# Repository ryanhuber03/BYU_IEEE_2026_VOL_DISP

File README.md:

# BYU_IEEE_2026_VOL_DISP
Volumetric Display for the BYU IEEE student branch, fall 2026.

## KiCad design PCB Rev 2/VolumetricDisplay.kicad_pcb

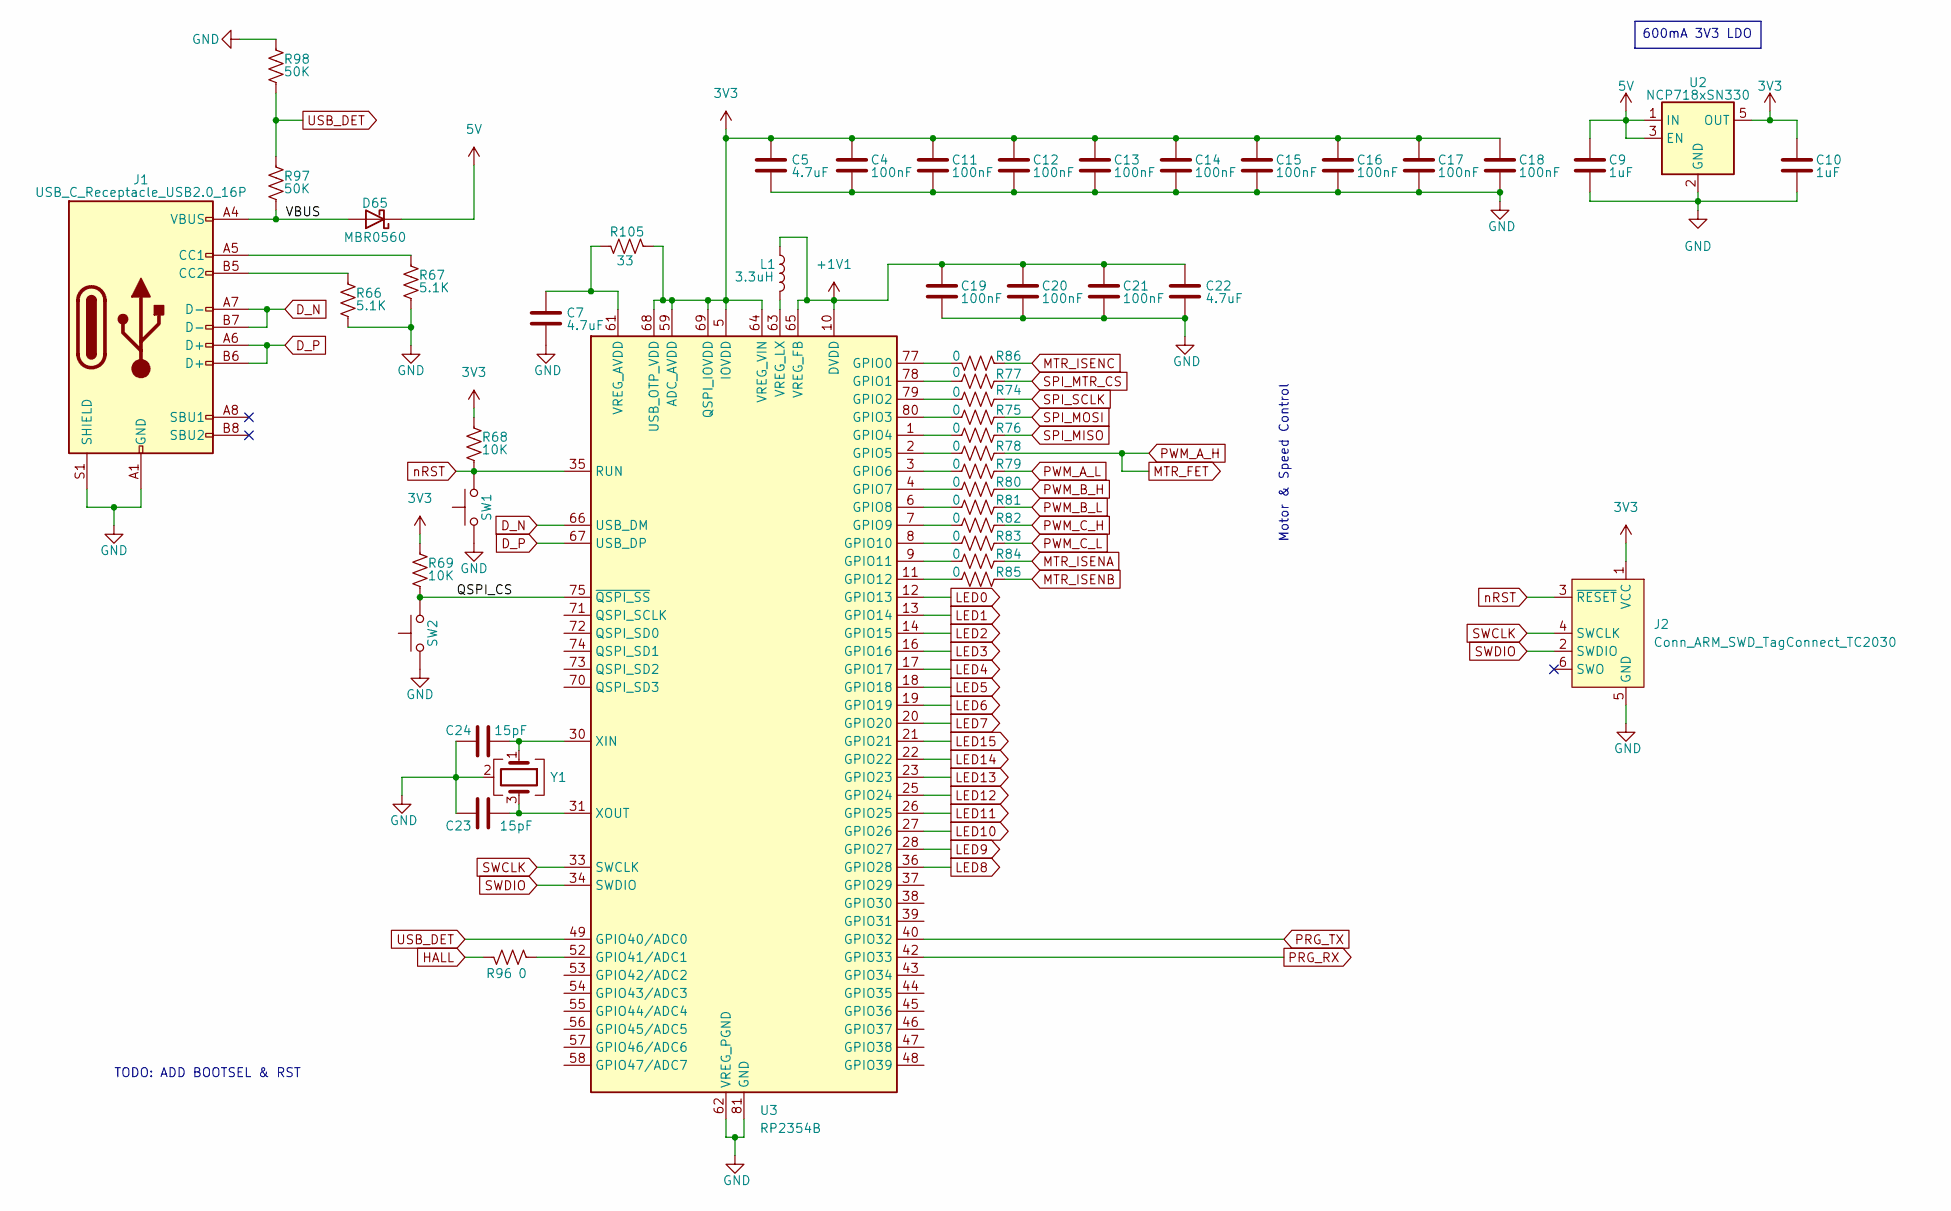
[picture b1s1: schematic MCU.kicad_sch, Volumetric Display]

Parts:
C4, C11, C12, C13, C14, C15, C16, C17, C18, C19, C20, C21: 100nF; C_0402_1005Metric_Pad0.74x0.62mm_HandSolder
C5, C7, C22: 4.7uF; C_0402_1005Metric_Pad0.74x0.62mm_HandSolder
C9, C10: 1uF; C_0603_1608Metric_Pad1.08x0.95mm_HandSolder
C23, C24: 15pF; C_0402_1005Metric_Pad0.74x0.62mm_HandSolder
D65: MBR0560; D_SOD-123
J1: USB_C_Receptacle_USB2.0_16P; USB_C_Receptacle_GCT_USB4085
J2: Conn_ARM_SWD_TagConnect_TC2030; Tag-Connect_TC2030-IDC-NL_2x03_P1.27mm_Vertical
L1: 3.3uH; L_0805_2012Metric_Pad1.05x1.20mm_HandSolder
R66, R67: 5.1K; R_0603_1608Metric_Pad0.98x0.95mm_HandSolder
R68, R69: 10K; R_0603_1608Metric_Pad0.98x0.95mm_HandSolder
R74, R75, R76, R77, R78, R79, R80, R81, R82, R83, R84, R85, R86, R96: 0; R_0603_1608Metric_Pad0.98x0.95mm_HandSolder
R97, R98: 50K; R_0603_1608Metric_Pad0.98x0.95mm_HandSolder
R105: 33; R_0603_1608Metric_Pad0.98x0.95mm_HandSolder
SW1, SW2: TS-1088-AR02016; SW_TS-1088-AR02016
U2: NCP718xSN330; SOT-23-5
U3: RP2354B; QFN-80-1EP_10x10mm_P0.4mm_EP3.4x3.4mm
Y1: Abracon ABM8-272-T3; Crystal_SMD_Abracon_ABM8G-4Pin_3.2x2.5mm

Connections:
3V3: C4.1, C5.1, C10.1, C11.1, C12.1, C13.1, C14.1, C15.1, C16.1, C17.1, C18.1, J2.1 (VCC), R68.2, R69.2, R105.1, U2.5 (OUT), U3.5 (IOVDD), U3.15 (IOVDD), U3.24 (IOVDD), U3.29 (IOVDD), U3.41 (IOVDD), U3.50 (IOVDD), U3.59 (ADC_AVDD), U3.60 (IOVDD), U3.64 (VREG_VIN), U3.68 (USB_OTP_VDD), U3.69 (QSPI_IOVDD), U3.76 (IOVDD); also elsewhere on the board
5V: C9.1, D65.1 (K), U2.1 (IN), U2.3 (EN); also elsewhere on the board
+1V1: C19.1, C20.1, C21.1, C22.1, L1.1, U3.10 (DVDD), U3.32 (DVDD), U3.51 (DVDD), U3.65 (VREG_FB)
/MCU/QSPI_CS: R69.1, SW2.2, U3.75 (~QSPI_SS)
/MCU/VBUS: D65.2 (A), J1.A4 (VBUS), J1.A9 (VBUS), J1.B4 (VBUS), J1.B9 (VBUS), R97.1
D_N: J1.A7 (D-), J1.B7 (D-), U3.66 (USB_DM)
D_P: J1.A6 (D+), J1.B6 (D+), U3.67 (USB_DP)
GND: C4.2, C5.2, C7.2, C9.2, C10.2, C11.2, C12.2, C13.2, C14.2, C15.2, C16.2, C17.2, C18.2, C19.2, C20.2, C21.2, C22.2, C23.1, C24.1, J1.A1 (GND), J1.A12 (GND), J1.B1 (GND), J1.B12 (GND), J1.S1 (SHIELD), J2.5 (GND), R66.1, R67.1, R98.2, SW1.1, SW2.1, U2.2 (GND), U3.62 (VREG_PGND), U3.81 (GND), Y1.2 (G), Y1.4 (G); also elsewhere on the board
HALL: R96.2; also elsewhere on the board
LED0: U3.12 (GPIO13); also elsewhere on the board
LED1: U3.13 (GPIO14); also elsewhere on the board
LED2: U3.14 (GPIO15); also elsewhere on the board
LED3: U3.16 (GPIO16); also elsewhere on the board
LED4: U3.17 (GPIO17); also elsewhere on the board
LED5: U3.18 (GPIO18); also elsewhere on the board
LED6: U3.19 (GPIO19); also elsewhere on the board
LED7: U3.20 (GPIO20); also elsewhere on the board
LED8: U3.36 (GPIO28); also elsewhere on the board
LED9: U3.28 (GPIO27); also elsewhere on the board
LED10: U3.27 (GPIO26); also elsewhere on the board
LED11: U3.26 (GPIO25); also elsewhere on the board
LED12: U3.25 (GPIO24); also elsewhere on the board
LED13: U3.23 (GPIO23); also elsewhere on the board
LED14: U3.22 (GPIO22); also elsewhere on the board
LED15: U3.21 (GPIO21); also elsewhere on the board
MTR_FET: R78.2; also elsewhere on the board
MTR_ISENA: R84.2; also elsewhere on the board
MTR_ISENB: R85.2; also elsewhere on the board
MTR_ISENC: R86.2; also elsewhere on the board
unnamed: J1.A5 (CC1), R67.2
unnamed: J1.B5 (CC2), R66.2
unnamed: R86.1, U3.77 (GPIO0)
unnamed: R77.1, U3.78 (GPIO1)
unnamed: R74.1, U3.79 (GPIO2)
unnamed: R75.1, U3.80 (GPIO3)
unnamed: R76.1, U3.1 (GPIO4)
unnamed: R78.1, U3.2 (GPIO5)
unnamed: R79.1, U3.3 (GPIO6)
unnamed: R80.1, U3.4 (GPIO7)
unnamed: R81.1, U3.6 (GPIO8)
unnamed: R82.1, U3.7 (GPIO9)
unnamed: R83.1, U3.8 (GPIO10)
unnamed: R84.1, U3.9 (GPIO11)
unnamed: R85.1, U3.11 (GPIO12)
unnamed: R96.1, U3.52 (GPIO41/ADC1)
unnamed: C7.1, R105.2, U3.61 (VREG_AVDD)
unnamed: L1.2, U3.63 (VREG_LX)
unnamed: C24.2, U3.30 (XIN), Y1.1
unnamed: C23.2, U3.31 (XOUT), Y1.3
PRG_RX: U3.42 (GPIO33)
PRG_TX: U3.40 (GPIO32)
PWM_A_L: R79.2; also elsewhere on the board
PWM_B_H: R80.2; also elsewhere on the board
PWM_B_L: R81.2; also elsewhere on the board
PWM_C_H: R82.2; also elsewhere on the board
PWM_C_L: R83.2; also elsewhere on the board
SPI_MISO: R76.2; also elsewhere on the board
SPI_MOSI: R75.2; also elsewhere on the board
SPI_MTR_CS: R77.2; also elsewhere on the board
SPI_SCLK: R74.2; also elsewhere on the board
SWCLK: J2.4 (SWCLK), U3.33 (SWCLK)
SWDIO: J2.2 (SWDIO), U3.34 (SWDIO)
USB_DET: R97.2, R98.1, U3.49 (GPIO40/ADC0)
nRST: J2.3 (~RESET), R68.1, SW1.2, U3.35 (RUN)

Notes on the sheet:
Motor & Speed Control
TODO: ADD BOOTSEL & RST
600mA 3V3 LDO

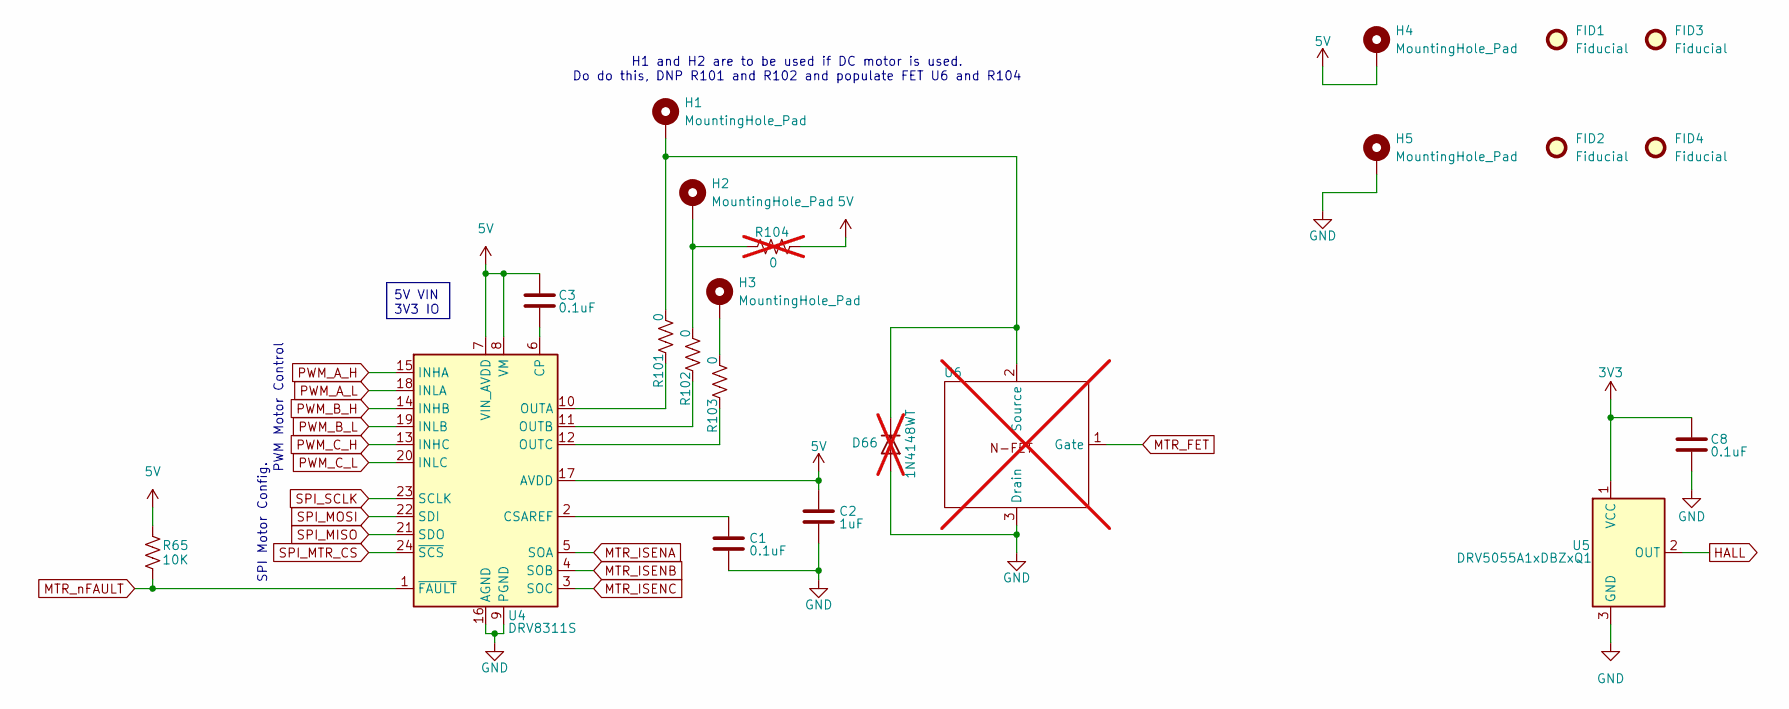
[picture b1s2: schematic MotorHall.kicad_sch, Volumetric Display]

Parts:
C1, C3: 0.1uF; C_0402_1005Metric_Pad0.74x0.62mm_HandSolder
C2: 1uF; C_0402_1005Metric_Pad0.74x0.62mm_HandSolder
C8: 0.1uF; C_0603_1608Metric_Pad1.08x0.95mm_HandSolder
D66: 1N4148WT; D_SOD-323_HandSoldering; not fitted
FID1, FID2, FID3, FID4: Fiducial; Fiducial_0.5mm_Mask1mm
H1, H2, H3, H4, H5: MountingHole_Pad; 28AWG Pad
R65: 10K; R_0603_1608Metric_Pad0.98x0.95mm_HandSolder
R101, R102, R103: 0; R_0603_1608Metric_Pad0.98x0.95mm_HandSolder
R104: 0; R_0603_1608Metric_Pad0.98x0.95mm_HandSolder; not fitted
U4: DRV8311S; Texas_RRW0024A_WQFN-24-1EP_3x3mm_P0.4mm_EP1.9x1.9mm
U5: DRV5055A1xDBZxQ1; SOT-23
U6: SOT-23_Handsoldering; not fitted

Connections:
3V3: C8.2, U5.1 (VCC); also elsewhere on the board
5V: C2.1, C3.2, H4.1 (1_1), R65.1, R104.1, U4.7 (VIN_AVDD), U4.8 (VM), U4.17 (AVDD); also elsewhere on the board
GND: C1.1, C2.2, C8.1, D66.2 (A), H5.1 (1_1), U4.9 (PGND), U4.16 (AGND), U4.25 (PGND), U5.3 (GND), U6.3 (Drain); also elsewhere on the board
HALL: U5.2 (OUT); also elsewhere on the board
MTR_FET: U4.15 (INHA), U6.1 (Gate); also elsewhere on the board
MTR_ISENA: U4.5 (SOA); also elsewhere on the board
MTR_ISENB: U4.4 (SOB); also elsewhere on the board
MTR_ISENC: U4.3 (SOC); also elsewhere on the board
MTR_nFAULT: R65.2, U4.1 (~FAULT)
unnamed: D66.1 (K), H1.1 (1_1), R101.1, U6.2 (Source)
unnamed: H2.1 (1_1), R102.1, R104.2
unnamed: H3.1 (1_1), R103.1
unnamed: C3.1, U4.6 (CP)
unnamed: C1.2, U4.2 (CSAREF)
unnamed: R101.2, U4.10 (OUTA)
unnamed: R102.2, U4.11 (OUTB)
unnamed: R103.2, U4.12 (OUTC)
PWM_A_L: U4.18 (INLA); also elsewhere on the board
PWM_B_H: U4.14 (INHB); also elsewhere on the board
PWM_B_L: U4.19 (INLB); also elsewhere on the board
PWM_C_H: U4.13 (INHC); also elsewhere on the board
PWM_C_L: U4.20 (INLC); also elsewhere on the board
SPI_MISO: U4.21 (SDO); also elsewhere on the board
SPI_MOSI: U4.22 (SDI); also elsewhere on the board
SPI_MTR_CS: U4.24 (~SCS); also elsewhere on the board
SPI_SCLK: U4.23 (SCLK); also elsewhere on the board

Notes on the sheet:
PWM Motor Control
H1 and H2 are to be used if DC motor is used. Do do this, DNP R101 and R102 and populate FET U6 and R104
SPI Motor Config.
5V VIN 3V3 IO

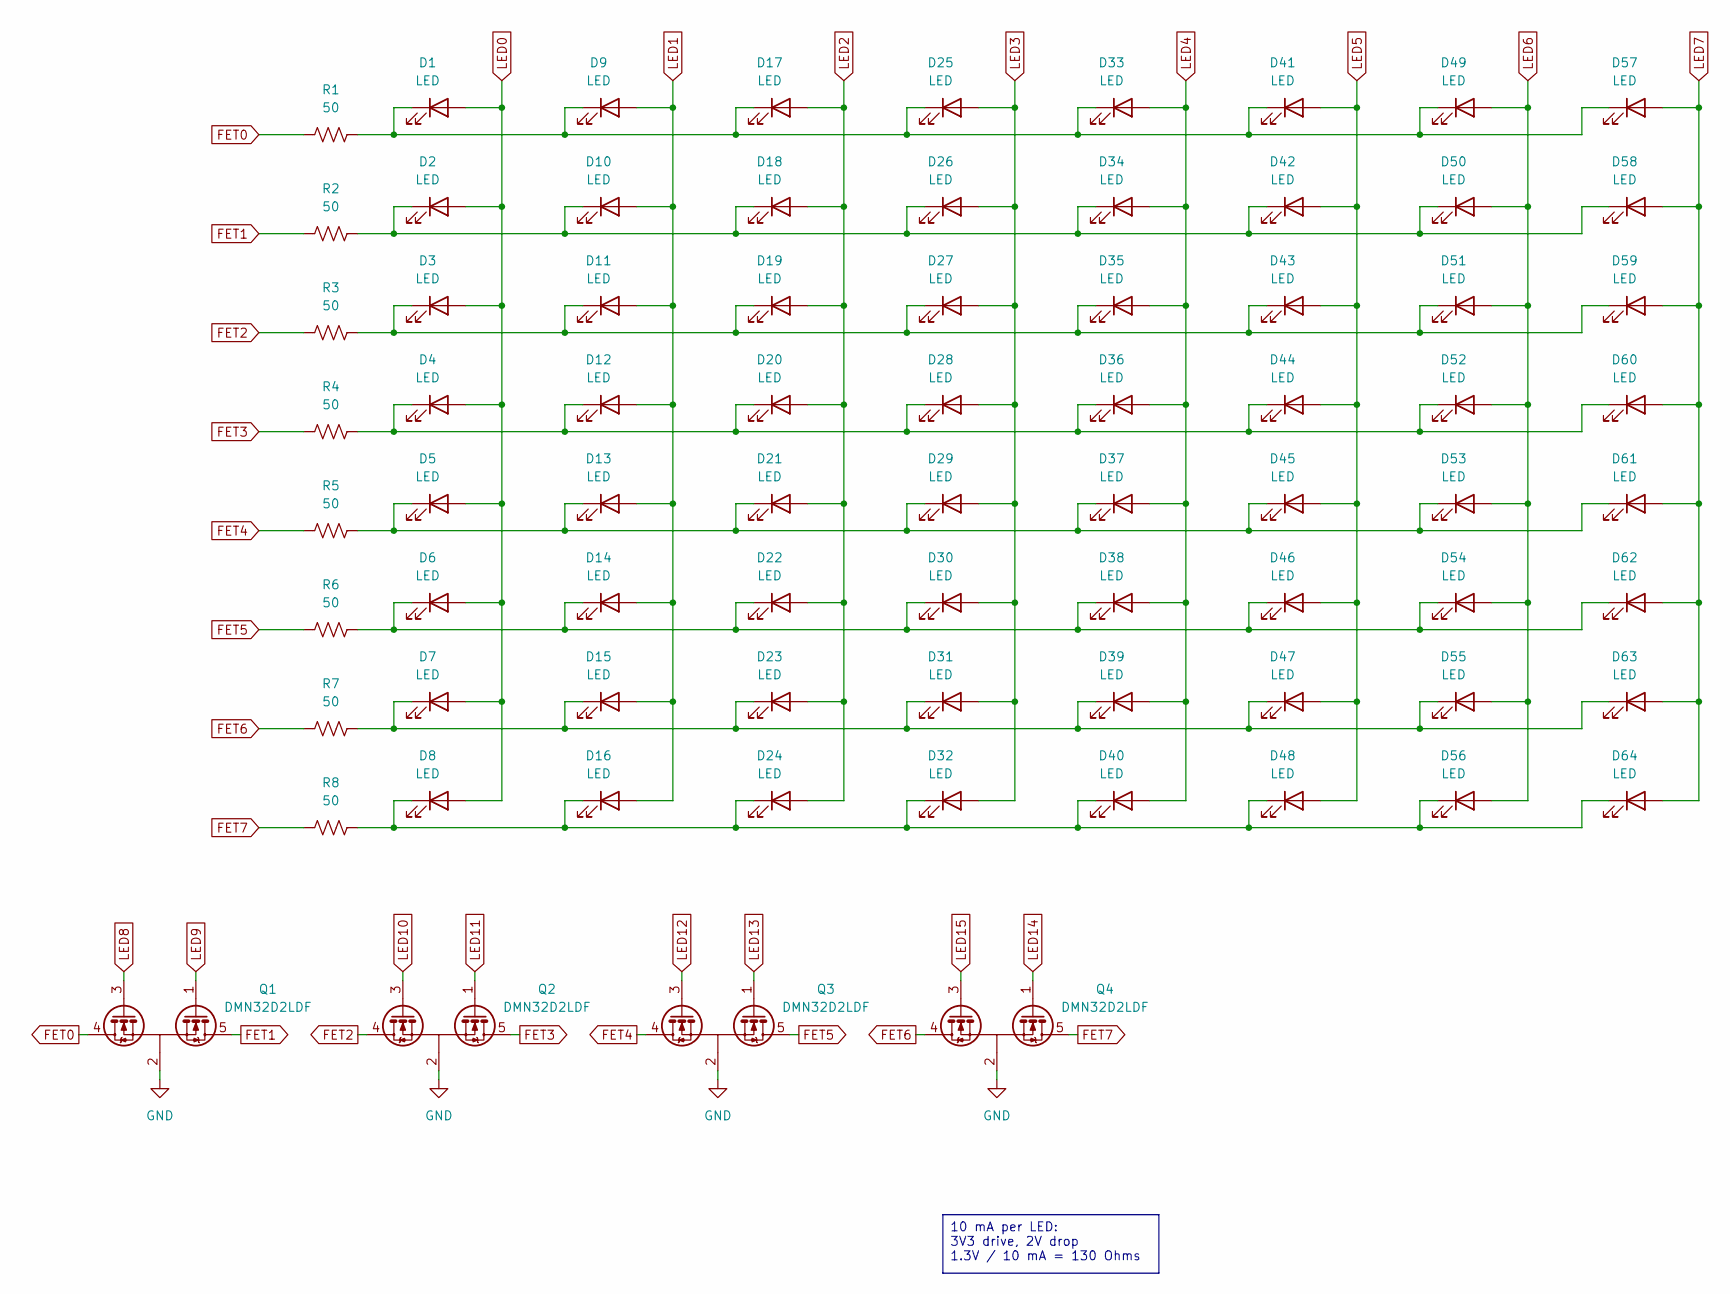
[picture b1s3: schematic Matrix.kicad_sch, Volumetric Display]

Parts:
D1, D2, D3, D4, D5, D6, D7, D8, D9, D10, D11, D12, D13, D14, D15, D16, D17, D18, D19, D20, D21, D22, D23, D24, D25, D26, D27, D28, D29, D30, D31, D32, D33, D34, D35, D36, D37, D38, D39, D40, D41, D42, D43, D44, D45, D46, D47, D48, D49, D50, D51, D52, D53, D54, D55, D56, D57, D58, D59, D60, D61, D62, D63, D64: LED; LED_0603_1608Metric_Pad1.05x0.95mm_HandSolder
Q1, Q2, Q3, Q4: DMN32D2LDF; SOT-353_SC-70-5
R1, R2, R3, R4, R5, R6, R7, R8: 50; R_0603_1608Metric_Pad0.98x0.95mm_HandSolder

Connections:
FET0: Q1.4 (D2), R1.1
FET1: Q1.5 (D1), R2.1
FET2: Q2.4 (D2), R3.1
FET3: Q2.5 (D1), R4.1
FET4: Q3.4 (D2), R5.1
FET5: Q3.5 (D1), R6.1
FET6: Q4.4 (D2), R7.1
FET7: Q4.5 (D1), R8.1
GND: Q1.2 (S), Q2.2 (S), Q3.2 (S), Q4.2 (S); also elsewhere on the board
LED0: D1.2 (A), D2.2 (A), D3.2 (A), D4.2 (A), D5.2 (A), D6.2 (A), D7.2 (A), D8.2 (A); also elsewhere on the board
LED1: D9.2 (A), D10.2 (A), D11.2 (A), D12.2 (A), D13.2 (A), D14.2 (A), D15.2 (A), D16.2 (A); also elsewhere on the board
LED2: D17.2 (A), D18.2 (A), D19.2 (A), D20.2 (A), D21.2 (A), D22.2 (A), D23.2 (A), D24.2 (A); also elsewhere on the board
LED3: D25.2 (A), D26.2 (A), D27.2 (A), D28.2 (A), D29.2 (A), D30.2 (A), D31.2 (A), D32.2 (A); also elsewhere on the board
LED4: D33.2 (A), D34.2 (A), D35.2 (A), D36.2 (A), D37.2 (A), D38.2 (A), D39.2 (A), D40.2 (A); also elsewhere on the board
LED5: D41.2 (A), D42.2 (A), D43.2 (A), D44.2 (A), D45.2 (A), D46.2 (A), D47.2 (A), D48.2 (A); also elsewhere on the board
LED6: D49.2 (A), D50.2 (A), D51.2 (A), D52.2 (A), D53.2 (A), D54.2 (A), D55.2 (A), D56.2 (A); also elsewhere on the board
LED7: D57.2 (A), D58.2 (A), D59.2 (A), D60.2 (A), D61.2 (A), D62.2 (A), D63.2 (A), D64.2 (A); also elsewhere on the board
LED8: Q1.3 (G2); also elsewhere on the board
LED9: Q1.1 (G1); also elsewhere on the board
LED10: Q2.3 (G2); also elsewhere on the board
LED11: Q2.1 (G1); also elsewhere on the board
LED12: Q3.3 (G2); also elsewhere on the board
LED13: Q3.1 (G1); also elsewhere on the board
LED14: Q4.1 (G1); also elsewhere on the board
LED15: Q4.3 (G2); also elsewhere on the board
unnamed: D1.1 (K), D9.1 (K), D17.1 (K), D25.1 (K), D33.1 (K), D41.1 (K), D49.1 (K), D57.1 (K), R1.2
unnamed: D2.1 (K), D10.1 (K), D18.1 (K), D26.1 (K), D34.1 (K), D42.1 (K), D50.1 (K), D58.1 (K), R2.2
unnamed: D3.1 (K), D11.1 (K), D19.1 (K), D27.1 (K), D35.1 (K), D43.1 (K), D51.1 (K), D59.1 (K), R3.2
unnamed: D4.1 (K), D12.1 (K), D20.1 (K), D28.1 (K), D36.1 (K), D44.1 (K), D52.1 (K), D60.1 (K), R4.2
unnamed: D5.1 (K), D13.1 (K), D21.1 (K), D29.1 (K), D37.1 (K), D45.1 (K), D53.1 (K), D61.1 (K), R5.2
unnamed: D6.1 (K), D14.1 (K), D22.1 (K), D30.1 (K), D38.1 (K), D46.1 (K), D54.1 (K), D62.1 (K), R6.2
unnamed: D7.1 (K), D15.1 (K), D23.1 (K), D31.1 (K), D39.1 (K), D47.1 (K), D55.1 (K), D63.1 (K), R7.2
unnamed: D8.1 (K), D16.1 (K), D24.1 (K), D32.1 (K), D40.1 (K), D48.1 (K), D56.1 (K), D64.1 (K), R8.2

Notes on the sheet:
10 mA per LED: 3V3 drive, 2V drop 1.3V / 10 mA = 130 Ohms

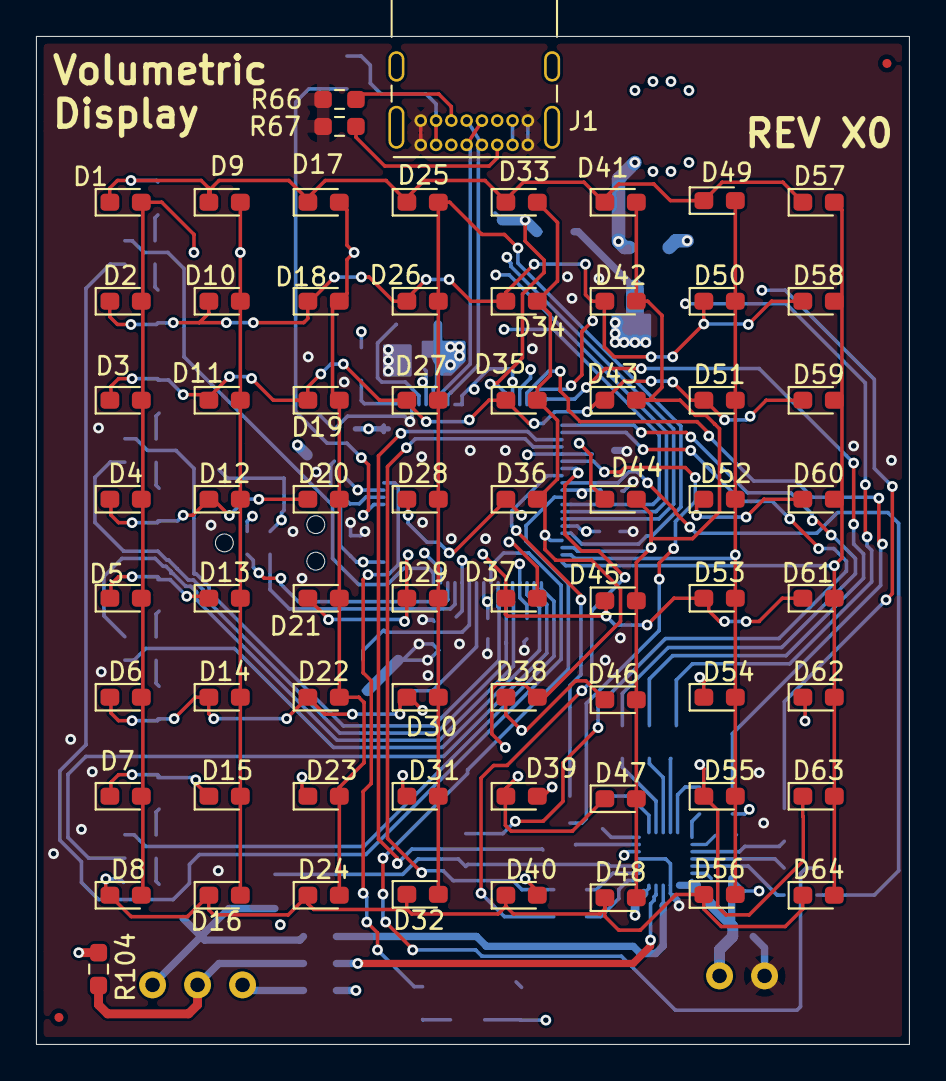
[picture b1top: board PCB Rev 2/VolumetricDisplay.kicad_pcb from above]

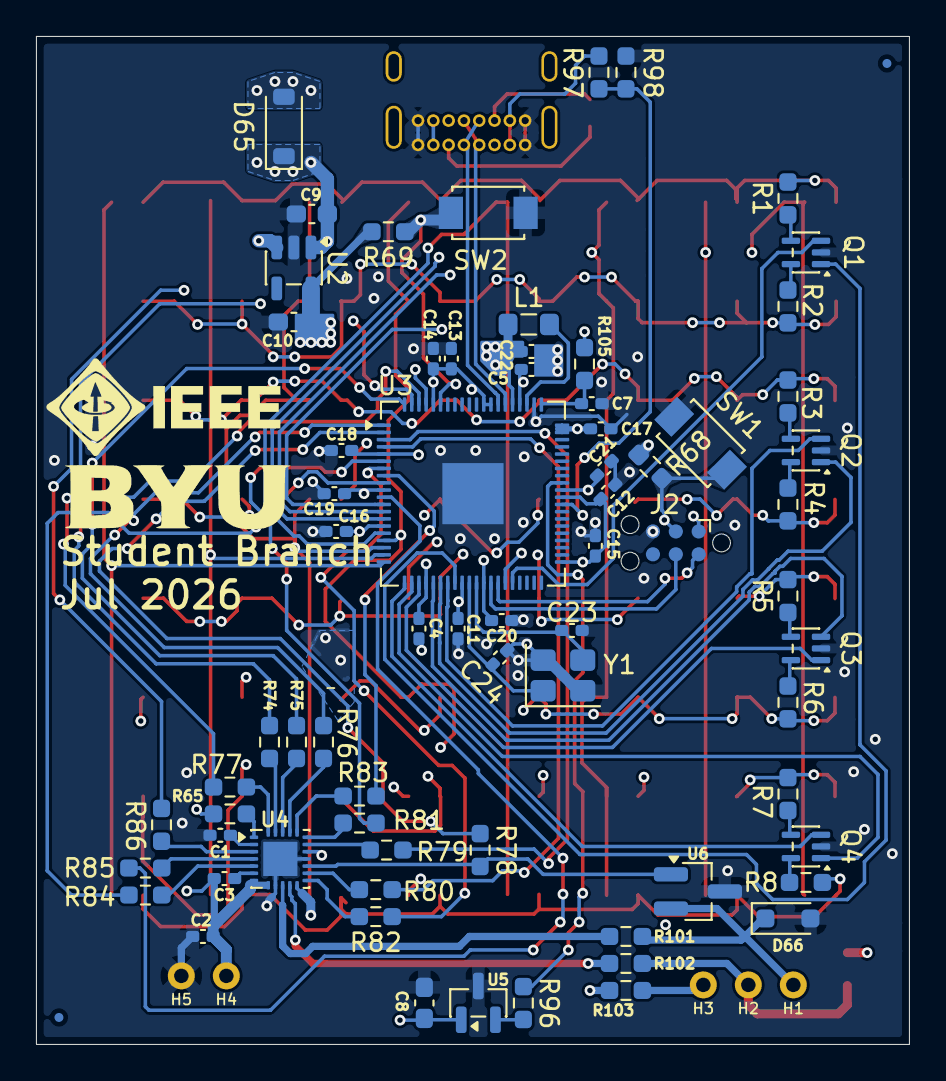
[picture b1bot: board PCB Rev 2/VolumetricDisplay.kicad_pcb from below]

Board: 4 copper layers, 48.5 x 56.0 mm, 147 parts (77 on the bottom side), 87 nets.

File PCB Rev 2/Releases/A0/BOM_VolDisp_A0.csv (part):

"Refs","Value","Footprint","Qty","DNP"
"C1","0.1uF","Capacitor_SMD:C_0402_1005Metric_Pad0.74x0.62mm_HandSolder","1",""
"C2","1uF","Capacitor_SMD:C_0402_1005Metric_Pad0.74x0.62mm_HandSolder","1",""
"C3","0.1uF","Capacitor_SMD:C_0402_1005Metric_Pad0.74x0.62mm_HandSolder","1",""
"C4","100nF","Capacitor_SMD:C_0402_1005Metric_Pad0.74x0.62mm_HandSolder","1",""
"C5","4.7uF","Capacitor_SMD:C_0402_1005Metric_Pad0.74x0.62mm_HandSolder","1",""
"C7","4.7uF","Capacitor_SMD:C_0402_1005Metric_Pad0.74x0.62mm_HandSolder","1",""
"C8","0.1uF","Capacitor_SMD:C_0603_1608Metric_Pad1.08x0.95mm_HandSolder","1",""
"C9","1uF","Capacitor_SMD:C_0603_1608Metric_Pad1.08x0.95mm_HandSolder","1",""
"C10","1uF","Capacitor_SMD:C_0603_1608Metric_Pad1.08x0.95mm_HandSolder","1",""
"C11","100nF","Capacitor_SMD:C_0402_1005Metric_Pad0.74x0.62mm_HandSolder","1",""
"C12","100nF","Capacitor_SMD:C_0402_1005Metric_Pad0.74x0.62mm_HandSolder","1",""
"C13","100nF","Capacitor_SMD:C_0402_1005Metric_Pad0.74x0.62mm_HandSolder","1",""
"C14","100nF","Capacitor_SMD:C_0402_1005Metric_Pad0.74x0.62mm_HandSolder","1",""
"C15","100nF","Capacitor_SMD:C_0402_1005Metric_Pad0.74x0.62mm_HandSolder","1",""
"C16","100nF","Capacitor_SMD:C_0402_1005Metric_Pad0.74x0.62mm_HandSolder","1",""
"C17","100nF","Capacitor_SMD:C_0402_1005Metric_Pad0.74x0.62mm_HandSolder","1",""
"C18","100nF","Capacitor_SMD:C_0402_1005Metric_Pad0.74x0.62mm_HandSolder","1",""
"C19","100nF","Capacitor_SMD:C_0402_1005Metric_Pad0.74x0.62mm_HandSolder","1",""
"C20","100nF","Capacitor_SMD:C_0402_1005Metric_Pad0.74x0.62mm_HandSolder","1",""
"C21","100nF","Capacitor_SMD:C_0402_1005Metric_Pad0.74x0.62mm_HandSolder","1",""
"C22","4.7uF","Capacitor_SMD:C_0402_1005Metric_Pad0.74x0.62mm_HandSolder","1",""
"C23","15pF","Capacitor_SMD:C_0402_1005Metric_Pad0.74x0.62mm_HandSolder","1",""
"C24","15pF","Capacitor_SMD:C_0402_1005Metric_Pad0.74x0.62mm_HandSolder","1",""
"D1","LED","LED_SMD:LED_0603_1608Metric_Pad1.05x0.95mm_HandSolder","1",""
"D2","LED","LED_SMD:LED_0603_1608Metric_Pad1.05x0.95mm_HandSolder","1",""
"D3","LED","LED_SMD:LED_0603_1608Metric_Pad1.05x0.95mm_HandSolder","1",""
"D4","LED","LED_SMD:LED_0603_1608Metric_Pad1.05x0.95mm_HandSolder","1",""
"D5","LED","LED_SMD:LED_0603_1608Metric_Pad1.05x0.95mm_HandSolder","1",""
"D6","LED","LED_SMD:LED_0603_1608Metric_Pad1.05x0.95mm_HandSolder","1",""
"D7","LED","LED_SMD:LED_0603_1608Metric_Pad1.05x0.95mm_HandSolder","1",""
"D8","LED","LED_SMD:LED_0603_1608Metric_Pad1.05x0.95mm_HandSolder","1",""
"D9","LED","LED_SMD:LED_0603_1608Metric_Pad1.05x0.95mm_HandSolder","1",""
"D10","LED","LED_SMD:LED_0603_1608Metric_Pad1.05x0.95mm_HandSolder","1",""
"D11","LED","LED_SMD:LED_0603_1608Metric_Pad1.05x0.95mm_HandSolder","1",""
"D12","LED","LED_SMD:LED_0603_1608Metric_Pad1.05x0.95mm_HandSolder","1",""
"D13","LED","LED_SMD:LED_0603_1608Metric_Pad1.05x0.95mm_HandSolder","1",""
"D14","LED","LED_SMD:LED_0603_1608Metric_Pad1.05x0.95mm_HandSolder","1",""
"D15","LED","LED_SMD:LED_0603_1608Metric_Pad1.05x0.95mm_HandSolder","1",""
"D16","LED","LED_SMD:LED_0603_1608Metric_Pad1.05x0.95mm_HandSolder","1",""
"D17","LED","LED_SMD:LED_0603_1608Metric_Pad1.05x0.95mm_HandSolder","1",""
"D18","LED","LED_SMD:LED_0603_1608Metric_Pad1.05x0.95mm_HandSolder","1",""
"D19","LED","LED_SMD:LED_0603_1608Metric_Pad1.05x0.95mm_HandSolder","1",""
"D20","LED","LED_SMD:LED_0603_1608Metric_Pad1.05x0.95mm_HandSolder","1",""
"D21","LED","LED_SMD:LED_0603_1608Metric_Pad1.05x0.95mm_HandSolder","1",""
"D22","LED","LED_SMD:LED_0603_1608Metric_Pad1.05x0.95mm_HandSolder","1",""
"D23","LED","LED_SMD:LED_0603_1608Metric_Pad1.05x0.95mm_HandSolder","1",""
"D24","LED","LED_SMD:LED_0603_1608Metric_Pad1.05x0.95mm_HandSolder","1",""
"D25","LED","LED_SMD:LED_0603_1608Metric_Pad1.05x0.95mm_HandSolder","1",""
"D26","LED","LED_SMD:LED_0603_1608Metric_Pad1.05x0.95mm_HandSolder","1",""
"D27","LED","LED_SMD:LED_0603_1608Metric_Pad1.05x0.95mm_HandSolder","1",""
"D28","LED","LED_SMD:LED_0603_1608Metric_Pad1.05x0.95mm_HandSolder","1",""
"D29","LED","LED_SMD:LED_0603_1608Metric_Pad1.05x0.95mm_HandSolder","1",""
"D30","LED","LED_SMD:LED_0603_1608Metric_Pad1.05x0.95mm_HandSolder","1",""
"D31","LED","LED_SMD:LED_0603_1608Metric_Pad1.05x0.95mm_HandSolder","1",""
"D32","LED","LED_SMD:LED_0603_1608Metric_Pad1.05x0.95mm_HandSolder","1",""
"D33","LED","LED_SMD:LED_0603_1608Metric_Pad1.05x0.95mm_HandSolder","1",""
"D34","LED","LED_SMD:LED_0603_1608Metric_Pad1.05x0.95mm_HandSolder","1",""
"D35","LED","LED_SMD:LED_0603_1608Metric_Pad1.05x0.95mm_HandSolder","1",""
"D36","LED","LED_SMD:LED_0603_1608Metric_Pad1.05x0.95mm_HandSolder","1",""
"D37","LED","LED_SMD:LED_0603_1608Metric_Pad1.05x0.95mm_HandSolder","1",""
"D38","LED","LED_SMD:LED_0603_1608Metric_Pad1.05x0.95mm_HandSolder","1",""
"D39","LED","LED_SMD:LED_0603_1608Metric_Pad1.05x0.95mm_HandSolder","1",""
"D40","LED","LED_SMD:LED_0603_1608Metric_Pad1.05x0.95mm_HandSolder","1",""
"D41","LED","LED_SMD:LED_0603_1608Metric_Pad1.05x0.95mm_HandSolder","1",""
"D42","LED","LED_SMD:LED_0603_1608Metric_Pad1.05x0.95mm_HandSolder","1",""
"D43","LED","LED_SMD:LED_0603_1608Metric_Pad1.05x0.95mm_HandSolder","1",""
"D44","LED","LED_SMD:LED_0603_1608Metric_Pad1.05x0.95mm_HandSolder","1",""
"D45","LED","LED_SMD:LED_0603_1608Metric_Pad1.05x0.95mm_HandSolder","1",""
"D46","LED","LED_SMD:LED_0603_1608Metric_Pad1.05x0.95mm_HandSolder","1",""
"D47","LED","LED_SMD:LED_0603_1608Metric_Pad1.05x0.95mm_HandSolder","1",""
"D48","LED","LED_SMD:LED_0603_1608Metric_Pad1.05x0.95mm_HandSolder","1",""
"D49","LED","LED_SMD:LED_0603_1608Metric_Pad1.05x0.95mm_HandSolder","1",""
"D50","LED","LED_SMD:LED_0603_1608Metric_Pad1.05x0.95mm_HandSolder","1",""
"D51","LED","LED_SMD:LED_0603_1608Metric_Pad1.05x0.95mm_HandSolder","1",""
"D52","LED","LED_SMD:LED_0603_1608Metric_Pad1.05x0.95mm_HandSolder","1",""
"D53","LED","LED_SMD:LED_0603_1608Metric_Pad1.05x0.95mm_HandSolder","1",""
"D54","LED","LED_SMD:LED_0603_1608Metric_Pad1.05x0.95mm_HandSolder","1",""
"D55","LED","LED_SMD:LED_0603_1608Metric_Pad1.05x0.95mm_HandSolder","1",""
"D56","LED","LED_SMD:LED_0603_1608Metric_Pad1.05x0.95mm_HandSolder","1",""
"D57","LED","LED_SMD:LED_0603_1608Metric_Pad1.05x0.95mm_HandSolder","1",""
"D58","LED","LED_SMD:LED_0603_1608Metric_Pad1.05x0.95mm_HandSolder","1",""
"D59","LED","LED_SMD:LED_0603_1608Metric_Pad1.05x0.95mm_HandSolder","1",""
"D60","LED","LED_SMD:LED_0603_1608Metric_Pad1.05x0.95mm_HandSolder","1",""
"D61","LED","LED_SMD:LED_0603_1608Metric_Pad1.05x0.95mm_HandSolder","1",""
"D62","LED","LED_SMD:LED_0603_1608Metric_Pad1.05x0.95mm_HandSolder","1",""
"D63","LED","LED_SMD:LED_0603_1608Metric_Pad1.05x0.95mm_HandSolder","1",""
"D64","LED","LED_SMD:LED_0603_1608Metric_Pad1.05x0.95mm_HandSolder","1",""
"D65","MBR0560","Diode_SMD:D_SOD-123","1",""
"D66","1N4148WT","Diode_SMD:D_SOD-323_HandSoldering","1","DNP"
"J1","USB_C_Receptacle_USB2.0_16P","Connector_USB:USB_C_Receptacle_GCT_USB4085","1",""
"L1","3.3uH","Inductor_SMD:L_0805_2012Metric_Pad1.05x1.20mm_HandSolder","1",""
"Q1","DMN32D2LDF","Package_TO_SOT_SMD:SOT-353_SC-70-5","1",""
"Q2","DMN32D2LDF","Package_TO_SOT_SMD:SOT-353_SC-70-5","1",""
"Q3","DMN32D2LDF","Package_TO_SOT_SMD:SOT-353_SC-70-5","1",""
"Q4","DMN32D2LDF","Package_TO_SOT_SMD:SOT-353_SC-70-5","1",""
"R1","50","Resistor_SMD:R_0603_1608Metric_Pad0.98x0.95mm_HandSolder","1",""
"R2","50","Resistor_SMD:R_0603_1608Metric_Pad0.98x0.95mm_HandSolder","1",""
"R3","50","Resistor_SMD:R_0603_1608Metric_Pad0.98x0.95mm_HandSolder","1",""
"R4","50","Resistor_SMD:R_0603_1608Metric_Pad0.98x0.95mm_HandSolder","1",""
"R5","50","Resistor_SMD:R_0603_1608Metric_Pad0.98x0.95mm_HandSolder","1",""
"R6","50","Resistor_SMD:R_0603_1608Metric_Pad0.98x0.95mm_HandSolder","1",""
"R7","50","Resistor_SMD:R_0603_1608Metric_Pad0.98x0.95mm_HandSolder","1",""
"R8","50","Resistor_SMD:R_0603_1608Metric_Pad0.98x0.95mm_HandSolder","1",""
"R65","10K","Resistor_SMD:R_0603_1608Metric_Pad0.98x0.95mm_HandSolder","1",""
"R66","5.1K","Resistor_SMD:R_0603_1608Metric_Pad0.98x0.95mm_HandSolder","1",""
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
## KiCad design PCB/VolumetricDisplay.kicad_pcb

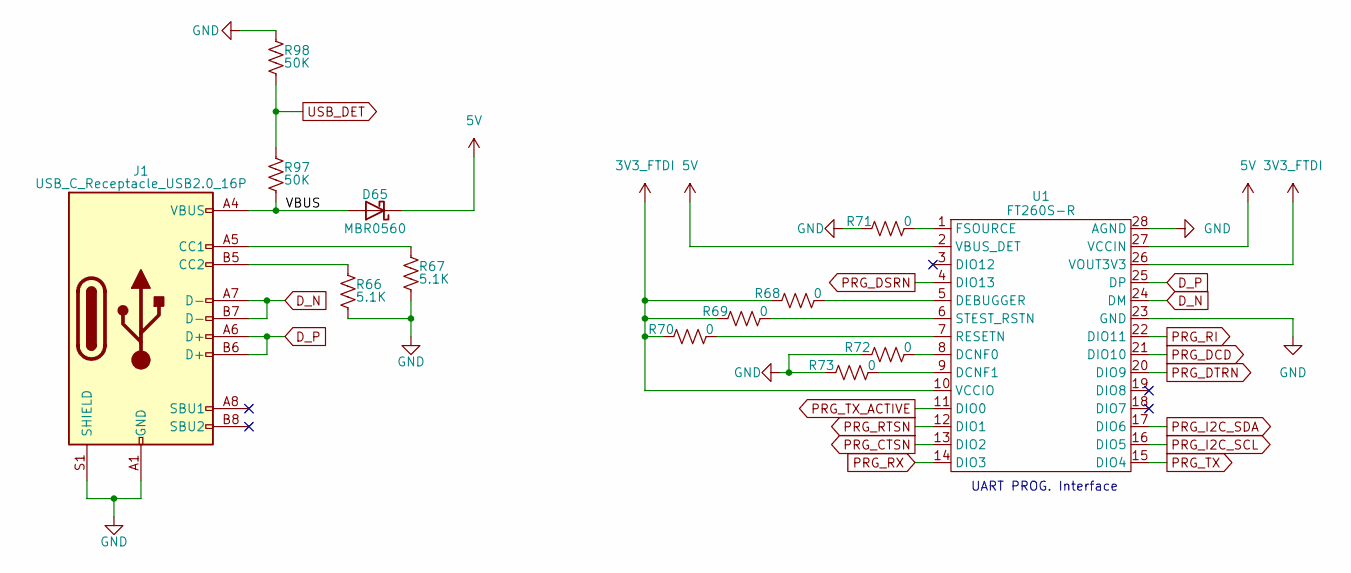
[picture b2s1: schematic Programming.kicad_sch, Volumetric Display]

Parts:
D65: MBR0560; D_SOD-123
J1: USB_C_Receptacle_USB2.0_16P; USB_C_Receptacle_GCT_USB4085
R66, R67: 5.1K; R_0603_1608Metric_Pad0.98x0.95mm_HandSolder
R68, R69, R70, R71, R72, R73: 0; R_0402_1005Metric_Pad0.72x0.64mm_HandSolder
R97, R98: 50K; R_0603_1608Metric_Pad0.98x0.95mm_HandSolder
U1: FT260S-R; TSSOP-28_4.4x9.7mm_P0.65mm

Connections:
3V3_FTDI: R68.1, R69.1, R70.1, U1.10 (VCCIO), U1.26 (VOUT3V3)
5V: D65.1 (K), U1.2 (VBUS_DET), U1.27 (VCCIN); also elsewhere on the board
/Programming/VBUS: D65.2 (A), J1.A4 (VBUS), J1.A9 (VBUS), J1.B4 (VBUS), J1.B9 (VBUS), R97.1
D_N: J1.A7 (D-), J1.B7 (D-), U1.24 (DM)
D_P: J1.A6 (D+), J1.B6 (D+), U1.25 (DP)
GND: J1.A1 (GND), J1.A12 (GND), J1.B1 (GND), J1.B12 (GND), J1.S1 (SHIELD), R66.1, R67.1, R71.1, R72.1, R73.1, R98.2, U1.23 (GND), U1.28 (AGND); also elsewhere on the board
unnamed: J1.A5 (CC1), R67.2
unnamed: J1.B5 (CC2), R66.2
unnamed: R72.2, U1.8 (DCNF0)
unnamed: R73.2, U1.9 (DCNF1)
unnamed: R68.2, U1.5 (DEBUGGER)
unnamed: R71.2, U1.1 (FSOURCE)
unnamed: R70.2, U1.7 (RESETN)
unnamed: R69.2, U1.6 (STEST_RSTN)
PRG_CTSN: U1.13 (DIO2); also elsewhere on the board
PRG_DCD: U1.21 (DIO10); also elsewhere on the board
PRG_DSRN: U1.4 (DIO13); also elsewhere on the board
PRG_DTRN: U1.20 (DIO9); also elsewhere on the board
PRG_I2C_SCL: U1.16 (DIO5)
PRG_I2C_SDA: U1.17 (DIO6)
PRG_RI: U1.22 (DIO11); also elsewhere on the board
PRG_RTSN: U1.12 (DIO1); also elsewhere on the board
PRG_RX: U1.14 (DIO3); also elsewhere on the board
PRG_TX: U1.15 (DIO4); also elsewhere on the board
PRG_TX_ACTIVE: U1.11 (DIO0); also elsewhere on the board
USB_DET: R97.2, R98.1; also elsewhere on the board

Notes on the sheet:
UART PROG. Interface
